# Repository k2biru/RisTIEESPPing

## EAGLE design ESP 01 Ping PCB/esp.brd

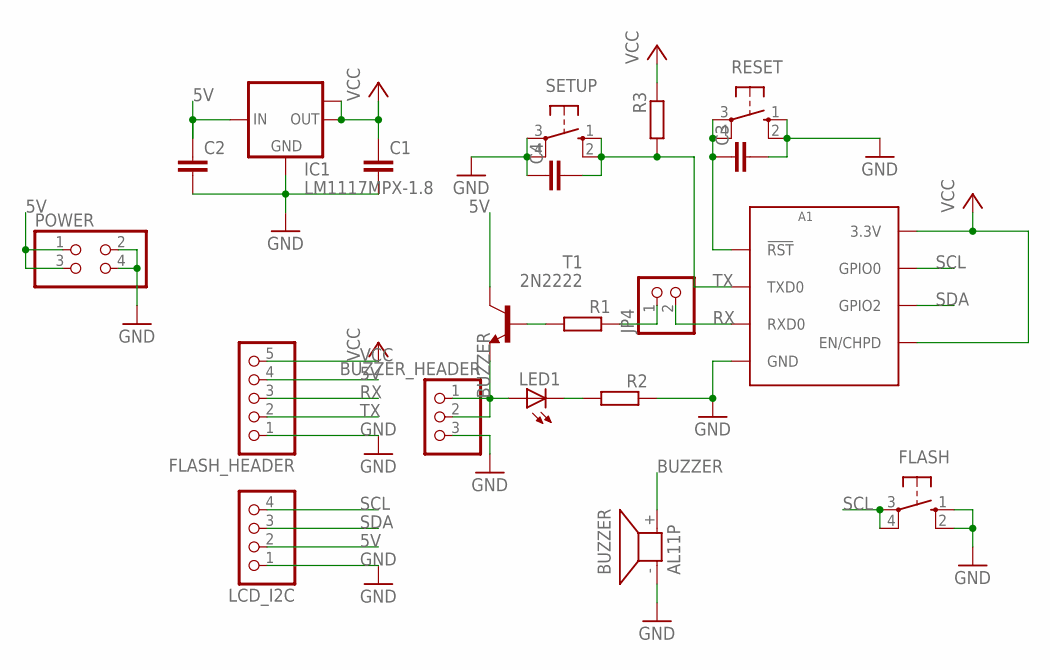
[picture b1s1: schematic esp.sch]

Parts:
A1: ESP8266_ESP-01; ESP8266_ESP-01_NO-SILKSCREEN
BUZZER: AL11P
BUZZER_HEADER: PINHD-1X3; 1X03
C1, C2, C3, C4: C-EU050-025X075; C050-025X075
FLASH: 10-XX; B3F-10XX
FLASH_HEADER: PINHD-1X5; 1X05
IC1: LM1117MPX-1.8; SOT223
JP4: PINHD-1X2; 1X02
LCD_I2C: PINHD-1X4; 1X04
LED1: LED5MM
POWER: PINHD-2X2; 2X02
R1, R2, R3: R-EU_0207/10; 0207/10
RESET: 10-XX; B3F-10XX
SETUP: 10-XX; B3F-10XX
T1: 2N2222; TO18

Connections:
5V: C2.1, FLASH_HEADER.4, IC1.3 (IN), LCD_I2C.2, POWER.1, POWER.3, T1.3 (C)
BUZZER: BUZZER.+ (2), BUZZER_HEADER.1, BUZZER_HEADER.2, LED1.A, T1.1 (E)
GND: A1.GND, BUZZER.- (1), BUZZER_HEADER.3, C1.2, C2.2, C3.2, C4.1, FLASH.1 (S), FLASH.2 (S1), FLASH_HEADER.1, IC1.1 (GND), LCD_I2C.1, POWER.2, POWER.4, R2.1, RESET.1 (S), RESET.2 (S1), SETUP.3, SETUP.4 (P1)
unnamed: JP4.1, R1.1
unnamed: R1.2, T1.2 (B)
unnamed: A1.RST (!RST!), C3.1, RESET.3, RESET.4 (P1)
unnamed: LED1.K (C), R2.2
RX: A1.RX (RXD0), FLASH_HEADER.3, JP4.2
SCL: A1.GPIO0, FLASH.3, FLASH.4 (P1), LCD_I2C.4
SDA: A1.GPIO2, LCD_I2C.3
TX: A1.TX (TXD0), C4.2, FLASH_HEADER.2, R3.2, SETUP.1 (S), SETUP.2 (S1)
VCC: A1.3V3 (3.3V), A1.EN/CH_PD (EN/CHPD), C1.1, FLASH_HEADER.5, IC1.2 (OUT), IC1.TAB (OUT1), R3.1

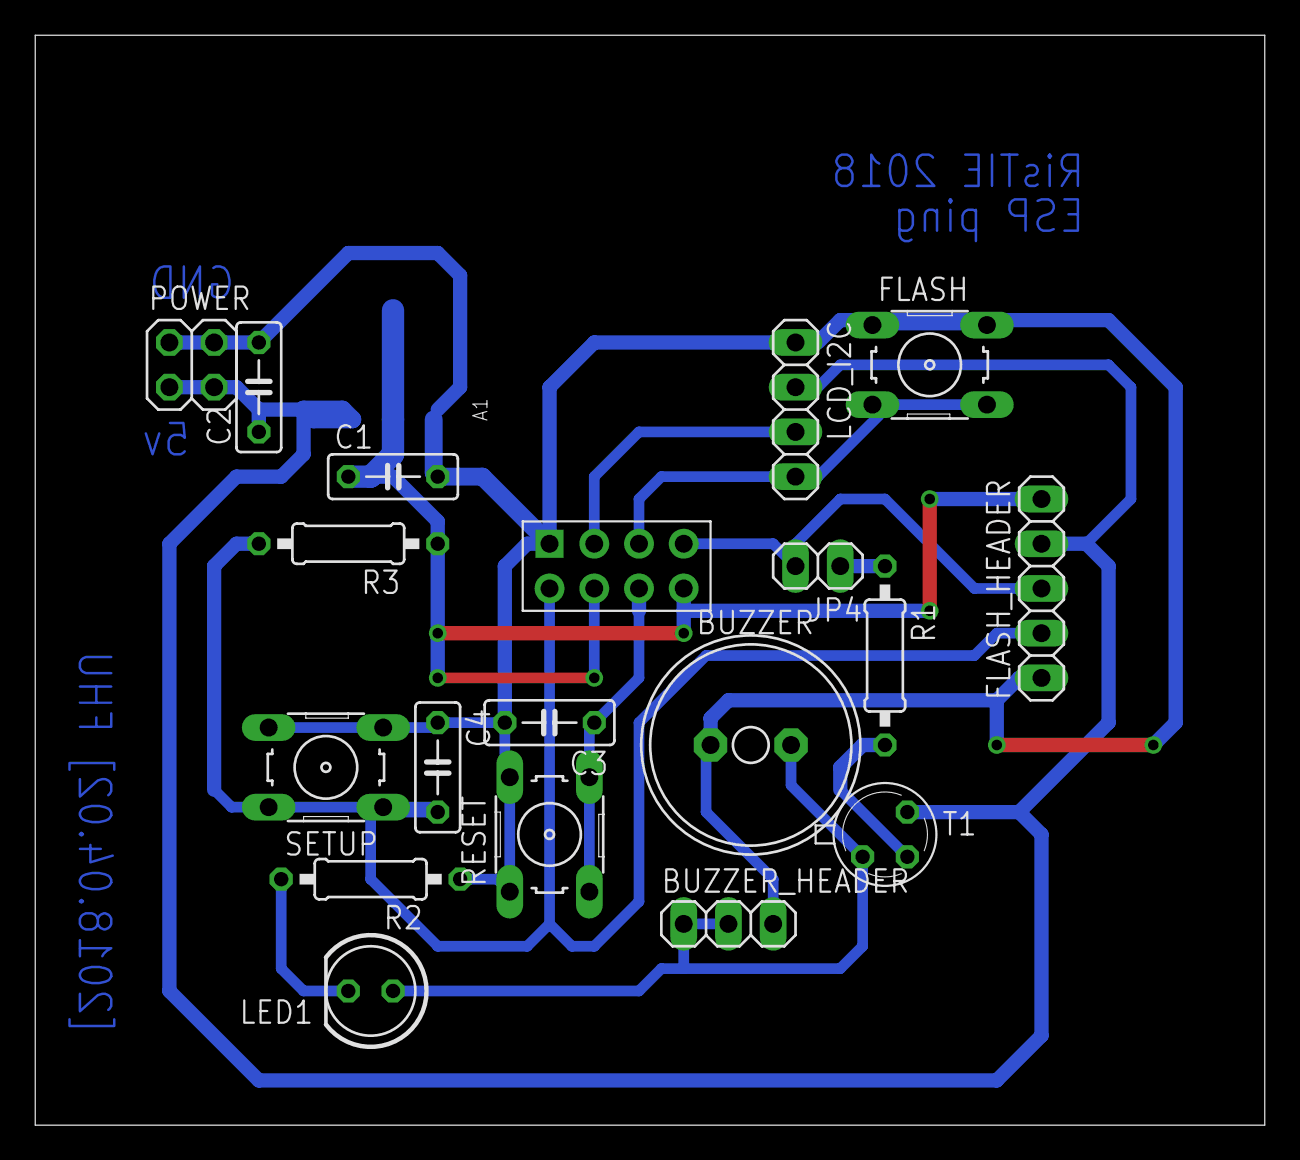
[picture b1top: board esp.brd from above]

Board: 2 copper layers, 69.8 x 61.9 mm, 20 parts (1 on the bottom side), 12 nets.
